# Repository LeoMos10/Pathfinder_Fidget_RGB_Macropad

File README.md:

# Pathfinder\_Fidget\_RGB\_Macropad

A custom 4-key RGB fidget game / macropad /carrier board for seed studio XIAO
[Prices screenshot](https://github.com/LeoMos10/Pathfinder_Fidget_RGB_Macropad/tree/main/ASSETS/prices)

[docs](DOCS.md)

## Parts: (all THT for easier assembly exept led)

* 4x Cherry MX style switches + keycaps(transparent for better effect)
* 4x SK6812MINI-E addressable RGB LEDs, one per each key
* Seeed Studio XIAO RP2040 microcontroller, mounted flat on the front of the board
* 2 layer PCB,  46mm x 63mm
* 2  JP pin header (optional for expanding the board)(2,5mm)
* 2 JP pin header (optiona for easier mounting the XIAO)(2,5mm)
* 4 ceramic condensator 100nF
* 5 resistors (1 × 330 Ω + 4 × 1 kΩ only if using mount holes as GPIO)
*  4x M4 screws (only if using mount hole as indeed)

###  PCB

The pbc was made in KiCad.

board:  46mm x 63mm

[interactive HTML mount guide (made with a KiCad extension)](production/ibom.html)

### Schematic

### PCB

Front copper and back copper in the editor (red is F.Cu, blue is B.Cu):

3D renders of the board:

## Firmware
[DOCS](DOCS.md)

## BOM
[CSV BOM with prices and links](production/bom.csv)
[Prices screenshot](https://github.com/LeoMos10/Pathfinder_Fidget_RGB_Macropad/tree/main/ASSETS/prices)

| Quantity | Name | Component| Footprint | Notes | 
| :-: | :--- | :--- | :--- | :--- | 
| 1 | U1 | Seeed Studio XIAO RP2040 | Modulo XIAO RP2040, 14 pin, passo 2.54 mm | Microcontrolloer| [seeedstudio.com](https://www.seeedstudio.com/XIAO-RP2040-p-5058.html) |
| 2 | J1a1, J1b1 | Pin header male 1×7 |  2.54 mm, vertical, THT | Optional| — |
| 4 | SW1–SW4 | Switch Cherry MX compatibile | PCB-mount, 5 pin, 1u | Switch| — |
| 4 | D1–D4 | SK6812MINI-E | RGB addressable, reverse-mount, 3.2 × 2.8 mm | LED RGB| — |
| 4 | C1–C4 | cermaic condesator 100 nF | THT, passo 2.50 mm, diametro 5 mm | Decopuling for led| — |
| 4 | R1–R4 | 1 kΩ resistor | 7.62 mm | Only if using mount holes as GPIO | — |
| 1 | R5 | Resistence 330 Ω | 7.62 mm | In serie sulla linea DIN dei LED | — |
| 4 | H1–H4 | screw M4 | 4.3 mm | Only if using mount holes as indeed | — |

- USE `SK6812MINI-E` reverse-mount, NOT `SK6812MINI`

total price:
with shipping and taxes:

## AI usage

AI was never used for:

* schematic design
* PCB design

*instead, it was used a little for:
*firmware and code

the drc rule
HARDWARE/kicad/path_finder.kicad_dru
## Extra stuff

easily soldable, perfect for beginners in soldering and coding

The contributors is both me

see [docs](DOCS.md)

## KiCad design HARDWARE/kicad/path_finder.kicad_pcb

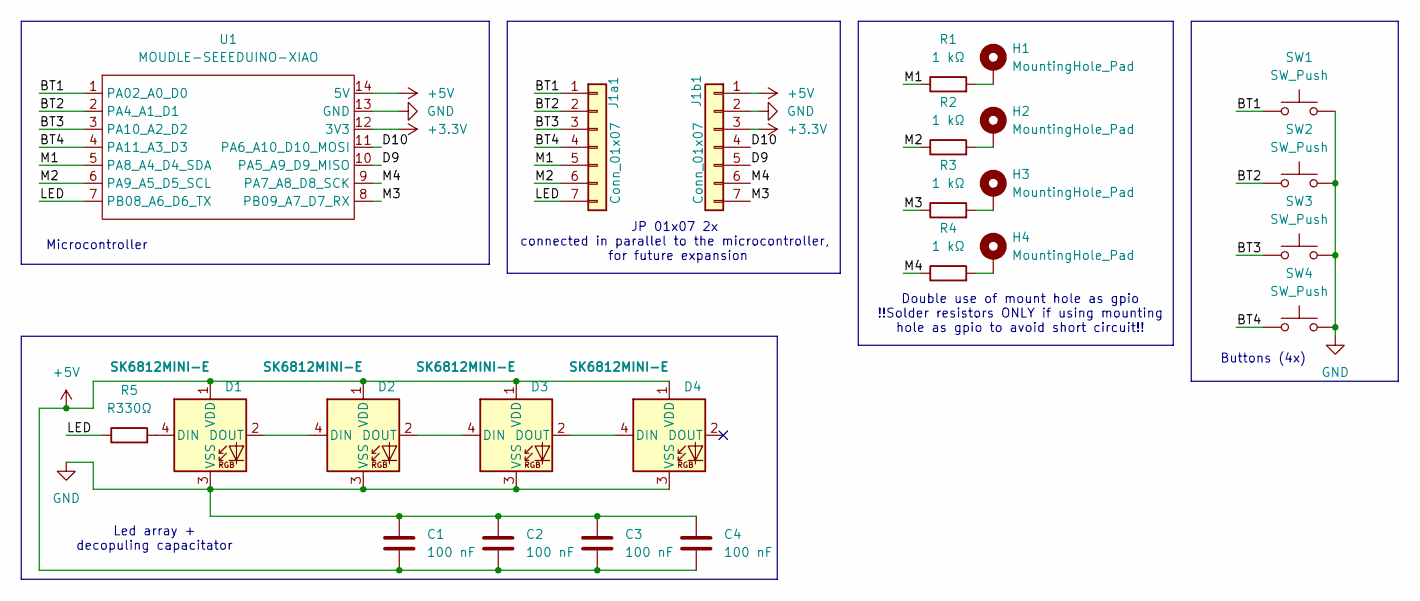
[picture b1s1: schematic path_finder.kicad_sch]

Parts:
C1, C2, C3, C4: 100 nF; C_Disc_D5.0mm_W2.5mm_P2.50mm
D1, D2, D3, D4: SK6812MINI-E; LED_SK6812MINI-E_3.2x2.8mm_P1.5mm_ReverseMount
H1, H2, H3, H4: MountingHole_Pad; MountingHole_4.3mm_M4_DIN965_Pad_TopBottom
J1a1, J1b1: Conn_01x07; PinHeader_1x07_P2.54mm_Vertical
R1, R2, R3, R4: 1 kΩ; R_Axial_DIN0207_L6.3mm_D2.5mm_P7.62mm_Horizontal
R5: R330Ω; R_Axial_DIN0207_L6.3mm_D2.5mm_P7.62mm_Horizontal
SW1, SW2, SW3, SW4: SW_Push; SW_Cherry_MX_1.00u_PCB
U1: MOUDLE-SEEEDUINO-XIAO; XIAO-Generic-Hybrid-14P-2.54-21X17.8MM

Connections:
+3.3V: J1b1.3, U1.12 (3V3)
+5V: C1.2, C2.2, C3.2, C4.2, D1.1 (VDD), D2.1 (VDD), D3.1 (VDD), D4.1 (VDD), J1b1.1, U1.14 (5V)
/BT1: J1a1.1, SW1.1, U1.1 (PA02_A0_D0)
/BT2: J1a1.2, SW2.1, U1.2 (PA4_A1_D1)
/BT3: J1a1.3, SW3.1, U1.3 (PA10_A2_D2)
/BT4: J1a1.4, SW4.1, U1.4 (PA11_A3_D3)
/D9: J1b1.5, U1.10 (PA5_A9_D9_MISO)
/D10: J1b1.4, U1.11 (PA6_A10_D10_MOSI)
/LED: J1a1.7, R5.1, U1.7 (PB08_A6_D6_TX)
/M1: J1a1.5, R1.1, U1.5 (PA8_A4_D4_SDA)
/M2: J1a1.6, R2.1, U1.6 (PA9_A5_D5_SCL)
/M3: J1b1.7, R3.1, U1.8 (PB09_A7_D7_RX)
/M4: J1b1.6, R4.1, U1.9 (PA7_A8_D8_SCK)
GND: C1.1, C2.1, C3.1, C4.1, D1.3 (VSS), D2.3 (VSS), D3.3 (VSS), D4.3 (VSS), J1b1.2, SW1.2, SW2.2, SW3.2, SW4.2, U1.13 (GND)
unnamed: D1.4 (DIN), R5.2
unnamed: D1.2 (DOUT), D2.4 (DIN)
unnamed: D2.2 (DOUT), D3.4 (DIN)
unnamed: D3.2 (DOUT), D4.4 (DIN)
unnamed: H1.1 (1_1), R1.2
unnamed: H2.1 (1_1), R2.2
unnamed: H3.1 (1_1), R3.2
unnamed: H4.1 (1_1), R4.2

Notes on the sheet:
Buttons (4x)
JP 01x07 2x connected in parallel to the microcontroller, for future expansion
Double use of mount hole as gpio !!Solder resistors ONLY if using mounting hole as gpio to avoid short circuit!!
Microcontroller
Led array + decopuling capacitator

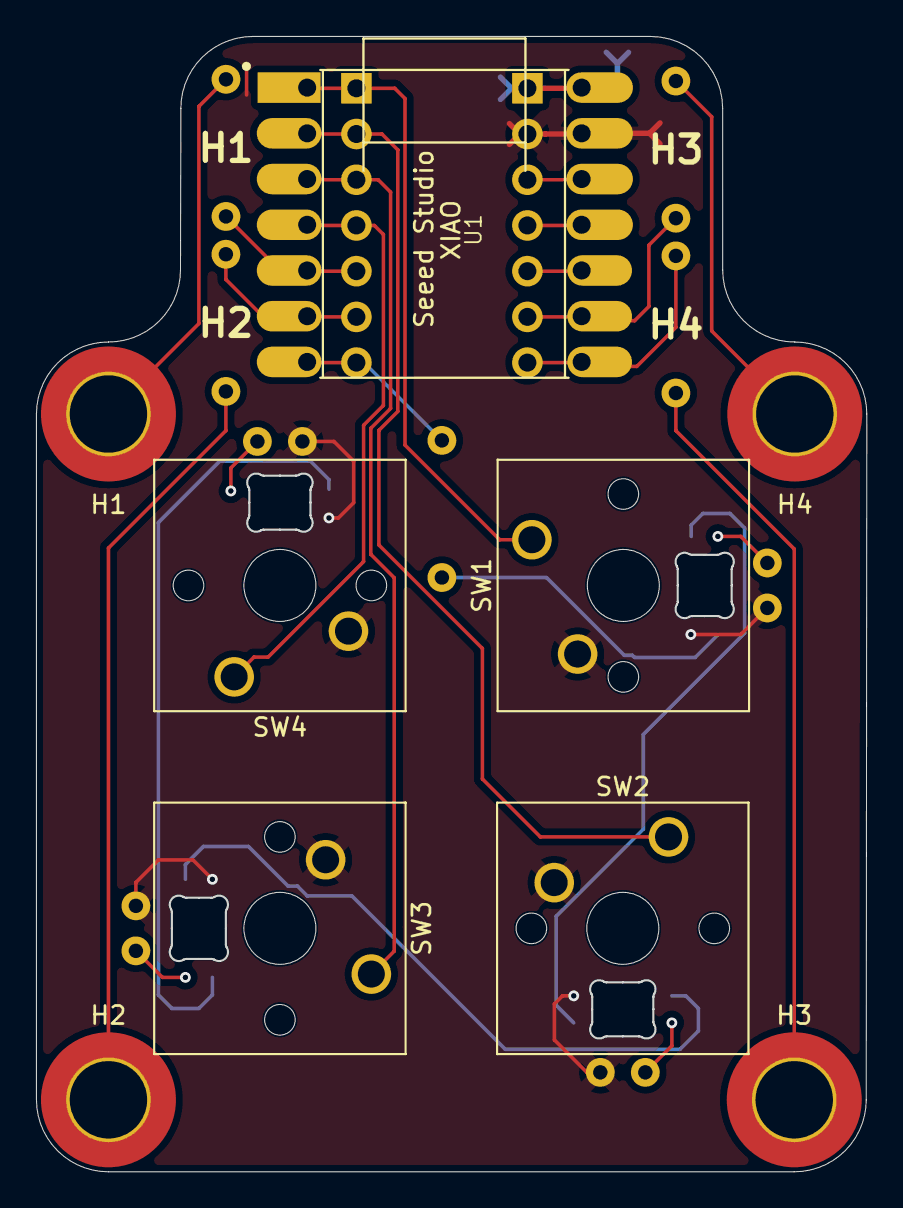
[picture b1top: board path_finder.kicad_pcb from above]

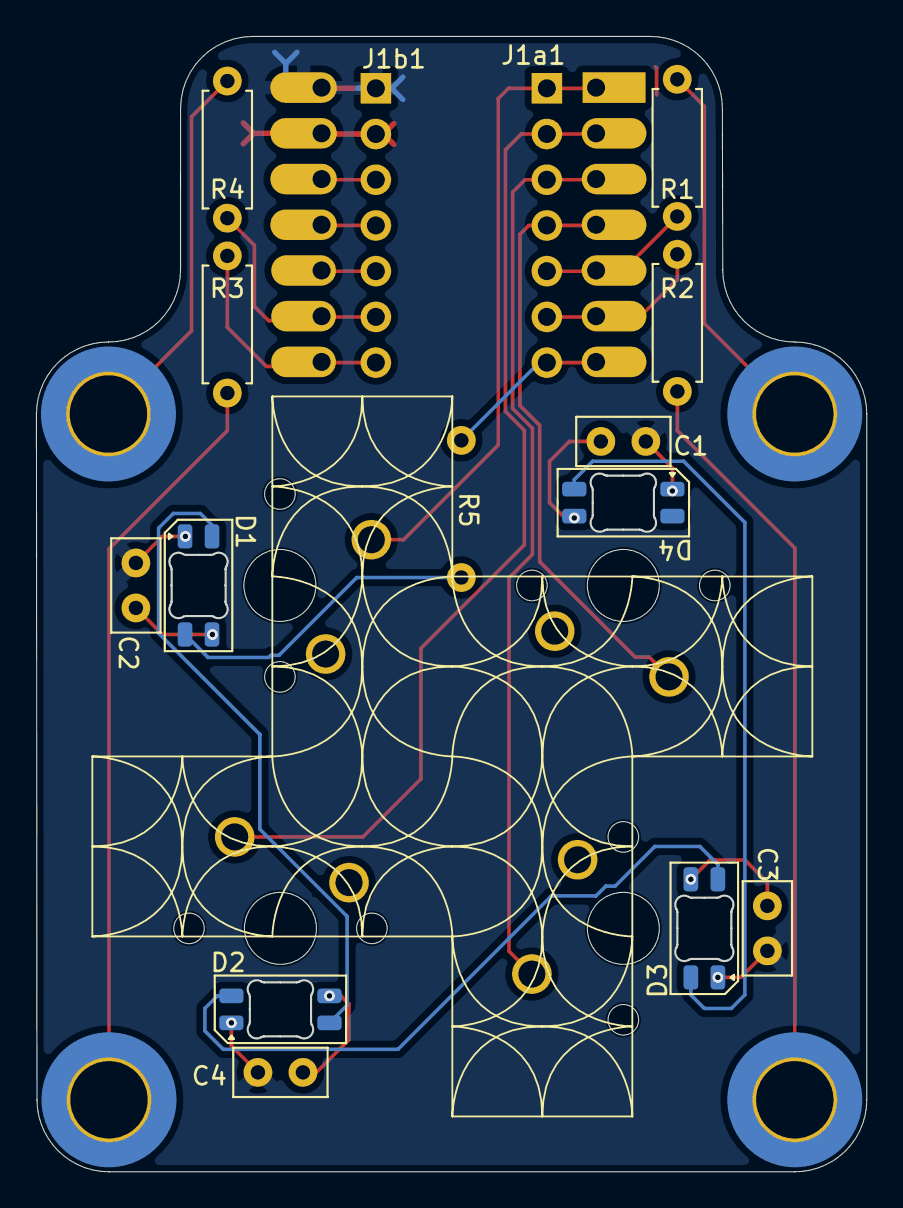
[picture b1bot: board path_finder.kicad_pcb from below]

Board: 2 copper layers, 46.1 x 63.1 mm, 24 parts (15 on the bottom side), 22 nets.
